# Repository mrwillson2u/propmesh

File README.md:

# PropMesh

Open-source wireless control for Halloween and holiday props.

Small ESP32 boards hidden in your props talk to each other by radio. A
sensor at the gate can set off a skeleton by the porch, a light show can
come on at dusk, and nothing needs wires across the lawn or an internet
connection. You set it all up from a web page, with no code.

**Using PropMesh?** Start at the docs site:
**[mrwillson2u.github.io/propmesh](https://mrwillson2u.github.io/propmesh/)**.
It has step-by-step guides, a page for each supported board, an installer
that puts the firmware on a board from your browser, and a copy of the
console you can try with no hardware.

This README is for people working on PropMesh itself.

> **Beta.** PropMesh runs the project's own yard for Halloween 2026 on
> off-the-shelf boards, and it changes quickly. Some features haven't
> been tried on real hardware yet. The docs site and
> [`docs/status.md`](docs/status.md) say which.

## What works today

The firmware runs on inexpensive ESP32 dev boards. You plug a board in,
open the console, and tell it what each pin does: relay, LED dimmer,
servo, DC motor, LED strip, or sensor. The board stores that and runs on
its own.

- **Mesh.** Boards pass messages to each other over ESP-NOW, so a far
  prop only needs to hear another board, not your WiFi. One board is the
  **bridge**: it connects the console to the mesh by USB or home WiFi and
  keeps the shared clock.
- **Shows.** Timed sequences across any outputs on any boards, triggers
  built as a graph (delay, cooldown, lockout, random pick, chains), a
  schedule tied to sunset, and STOP ALL. The show is stored on the boards
  and keeps running with the laptop closed.
- **Lights.** WS2812 and SK9822/APA102 strips, a fire effect, and BRMesh
  Bluetooth flood lights paired straight from the console.
- **Updates over the air,** through the mesh or over WiFi, resumable,
  with automatic rollback.
- **Battery boards.** Deep sleep, check-ins on a shared clock grid, and
  an optional repeater mode that relays while the show runs.
- **Yard view.** Mesh health by signal strength, and a map of your yard
  you can draw on.

| Board | Status |
|---|---|
| ESP32 DevKit V1 (30-pin) | Runs the project's yard |
| Adafruit HUZZAH32 Feather | Partly tested |
| ESP32-C6 SuperMini | Built, not yet flashed |
| ESP32-C3 SuperMini | Built, not yet flashed |

Each board's page on the docs site has the details. To support another
board, see [Adding a board](#adding-a-board).

## PropMesh's own boards (in design)

Two purpose-built boards run the same firmware and console. The PCBs
come after Halloween 2026, aiming at the 2027 season. Designs are in
[`hardware/`](hardware/) under CERN-OHL-S.

| | **PropMesh Pro** | **PropMesh Mini** |
|---|---|---|
| For | a prop that does everything | a small prop on a battery |
| MCU | ESP32-S3-WROOM-1 / 1U (N8R2) | ESP32-S3-WROOM-1U-N16R2 |
| Power | 12–30 V DC | 1S Li-ion |
| Motors | 2 stepper sockets (each can run 2 brushed DC) + 2 brushed DC | — |
| Servos | 6 | pending |
| Relays (dry contact, 30 V max) | 3 | pending |
| Addressable LED | 2 (3- or 4-wire) | pending |
| Dimmable LED | 6 | pending |
| Sensors | 3 digital, 2 analog | pending |
| Audio | I²S + microSD | I²S, sounds stored in flash |
| State | schematic done; layout next | module chosen; pin allocation being redone for the S3 |

"Pending" means the Mini's earlier ESP32-C3 plan was replaced on
2026-09-19 and its new allocation isn't finished. Neither board switches
mains power. That is a design decision; see [`CLAUDE.md`](CLAUDE.md).

## Origins

PropMesh grew out of one-off prop controllers built for the 2024 and
2025 seasons: a painlessMesh network of ESP32-C3s, a stepper-driven prop
lid, a fire-effect lantern, and a bridge for Bluetooth flood lights.
Those prototypes are kept in [`reference/`](reference/), with
credentials removed. This repository started in September 2026 to turn
them into one system.

## How it is tested

A feature counts as done when it has run on real boards. The host test
suite (`firmware/test/`) covers the pure logic: pin rules, show
scheduling, sunrise and sunset, ramps, mesh framing and reassembly.
Bench results, with dates and numbers, are recorded in
[`docs/generic-boards.md`](docs/generic-boards.md) next to each
feature's design; anything that has not yet run on hardware is marked
there, in [`docs/status.md`](docs/status.md), and on the docs site.

## Repository layout

```
docs/status.md          START HERE: where things stand, what's next, bench tests waiting
docs/generic-boards.md  the firmware that runs today: design, APIs, bench results per feature
docs/software-plan.md   architecture, mesh protocol, console plan, licensing
docs/hardware-spec.md   Pro and Mini: BOM, costs, mechanical, manufacturing

firmware/node/          the node firmware (PlatformIO), one env per board profile
firmware/common/        shared code: propmesh/ (mesh core, pure logic, generated
                        headers) and propmesh-node/ (drivers, API, sleep, OTA, sync)
firmware/test/          host tests (pio test -e native)
firmware/mesh-node/     the early ESP-NOW testbed (Sept 2026), kept building in CI

console/                the web console (Vite + React + TypeScript), with a simulator
website/                the docs site (Astro Starlight), browser flasher, screenshots

boards/                 SOURCE OF TRUTH: what each pin of a supported dev board can do
pinmap.yaml             SOURCE OF TRUTH: Pro / Mini pin assignments
schema/messages.yaml    SOURCE OF TRUTH: mesh messages and enums

tools/                  generators (genboards, genmsg, genpins), bridge.py, ota_serve.py,
                        and KiCad helpers for the hardware (checknet, checksetup, …)
hardware/               KiCad projects for the Pro and the Mini
reference/              pre-PropMesh prototypes (2024–25), scrubbed; see its README
```

Generated files are never edited by hand. Edit the source, regenerate,
and commit both. CI fails if they disagree.

```
python3 tools/genboards.py     # boards/*.yaml   -> boards_gen.h, boards_gen.ts
python3 tools/genmsg.py        # schema/*.yaml   -> proto_gen.h, proto_gen.ts
python3 tools/genpins.py       # pinmap.yaml     -> pins_*.h
# add --check to verify instead of write
```

## Getting started as a developer

You need Python 3, Node 22, and PlatformIO.

```
git clone https://github.com/mrwillson2u/propmesh.git && cd propmesh
git checkout dev
python3 -m venv .venv && . .venv/bin/activate
pip install -r requirements.txt platformio pyserial
npm ci --prefix console && npm ci --prefix website
```

**Firmware**

```
pio test -d firmware/test -e native                         # host tests
pio run  -d firmware/node -e esp32-devkit-v1                # build
pio run  -d firmware/node -e esp32-devkit-v1 -t upload      # flash a board on USB
```

Board envs: `esp32-devkit-v1`, `esp32-huzzah32`, `esp32-c6-supermini`,
`esp32-c3-supermini`. On Linux, USB serial needs your user in the
`dialout` group.

**Console**

```
npm run dev --prefix console        # then open http://localhost:5173/?sim=1
```

`?sim=1` connects to a simulated bridge with two boards behind it, so you
can work on the UI with no hardware. USB connections need Chrome or Edge.

**Docs site**

```
npm run dev --prefix website        # http://localhost:4321/propmesh/
```

`website/README.md` covers the board pages, the flasher, the screenshots
and how to write a page.

**Talking to a live mesh from a terminal**

```
python3 tools/bridge.py --host propmesh.local status
```

This reaches the bridge over WiFi, so nothing gets reset by opening a USB
port. `docs/status.md` §5 covers working on a separate server, tunnels,
and serving firmware for updates.

## Adding a board

A board works with PropMesh once it has a **profile**: a YAML file in
[`boards/`](boards/) listing what each pin can do and what to warn about.

1. Copy an existing profile and fill it in from the seller's pinout and
   the chip datasheet's strapping-pin table.
2. Add its `board_type` to `BoardType` in `schema/messages.yaml`.
3. Run `python3 tools/genmsg.py && python3 tools/genboards.py`. The
   generator refuses advice the pin can't follow.
4. Add an env to `firmware/node/platformio.ini` with
   `-DPM_BOARD_PROFILE=PM_BOARD_<ID>`.

The board's page on the docs site and its pinout in the console are
generated from the same file. Not comfortable doing this? Use the
[board request form](https://github.com/mrwillson2u/propmesh/issues/new?template=board-request.yml).

## Contributing

Pull requests go to **`dev`**. `main` only takes PRs from `dev` and
publishes the docs site. Read [`CONTRIBUTING.md`](CONTRIBUTING.md) first:
it has the checks to run and the sign-off each commit needs.

The decisions in [`CLAUDE.md`](CLAUDE.md) under "Locked design decisions"
were settled after analysis. To change one, say why its reasoning no
longer holds. Bugs, questions and reports from real yards go in
[issues](https://github.com/mrwillson2u/propmesh/issues).

## License

Copyleft open source: use it, change it, sell things built with it, but
share your changes and keep the credit. Details and reasoning:
[`LICENSING.md`](LICENSING.md).

| Part | License |
|---|---|
| Firmware, tools, board profiles | GPL-3.0-or-later |
| Console (web app) | AGPL-3.0-or-later |
| Board designs (`hardware/`) | CERN-OHL-S-2.0 |
| Docs and the docs site's text | CC BY-SA 4.0 |

The PropMesh name and logo: [`TRADEMARK.md`](TRADEMARK.md). Credits and
third-party code: [`THIRD_PARTY.md`](THIRD_PARTY.md).

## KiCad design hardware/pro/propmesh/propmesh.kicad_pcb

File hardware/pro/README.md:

# PropMesh Pro — start here

KiCad project: `propmesh/`. This file is the **map** — if you ever need
two documents open at once to do one task, that's a bug in the docs;
fix the doc, don't cross-reference.

## The four layers

| Layer | Lives in | Open it when |
|---|---|---|
| **WHY** — decisions, costs, schedule | `docs/hardware-spec.md` | you're questioning a choice or pricing something. Its BOM tables are **cost rollups, not orderable specs.** |
| **WHAT** — every pin and net name | `pinmap.yaml` (repo root) | never during capture — each sheet file below already quotes its nets. Edit it only to *change* an assignment (then regenerate + update spec, same commit). |
| **HOW (layout)** — placing and routing the board | **`layout.md`** | laying out the PCB as one numbered procedure (Part A: Board Setup, outline, holes, every connector's Position X/Y, block regions, per-part placement tables, zones, routing, silk, DRC, export) with a "where you are" line at the top; Part B is the reference behind it. `tools/checksetup.py` verifies the setup steps from the saved files. |
| **HOW** — drawing each schematic sheet | **`sheets/NN-*.md`** | drawing that sheet. Each is self-contained: parts, selection criteria, supporting passives, exact net names, a done-checklist. |
| **PROCESS** — review, libraries, git | `CLAUDE.md` (review order), `hardware/README.md` (libraries, easyeda2kicad, what's committed) | reviewing, importing a part, committing. |
| **AUDIT** — the last full review | **`review-2026-09-08.md`** | before routing, and before ordering. One pre-route audit of schematic + placement + every datasheet: what must be fixed first, what was verified correct, and what to check at bring-up. |

**The standing rule:** anything learned during capture — a criteria
gotcha, a stock problem, a changed value — goes into the relevant
`sheets/` file the same day. Chat sessions and heads are not storage.

**Connections live in `NN-name.net.yaml`, one line per net — never in
prose or markdown tables — and are DRAWN, not described.**
`tools/checknet.py NN.net.yaml --mermaid` renders it to
`NN.diagram.html` (open in any browser) and `NN.diagram.md`: one
left-to-right wiring diagram per circuit block, every part's GND pin
written in its box, plus a per-net roll-call table. That is the drawing
guide Colin works from — visual, not prose. **A multi-unit symbol (quad
gate, dual op-amp) must carry `units: {A: [pins], …}` in its yaml** so
the diagram draws one box per unit, matching the separate symbols KiCad
places — sheet 05's 74AHCT125 rendered as one 14-pin box first, and
was undrawable from (2026-09-05). The markdown says *why*; the
yaml says *what wires to what*, and it is machine-checked:

```
python3 tools/checknet.py hardware/pro/sheets/01-power.net.yaml
```

diffs the spec against `kicad-cli`'s netlist export of the real
schematic **and writes `NN.check.html` — the same diagram coloured by
result** (green ok, red wrong net with a note saying where the pin
actually is, orange wrong value, dashed not placed). Open it in a
browser, not the editor; all green = sheet done. Parts match by
**Value**, and each spec part is paired with one specific KiCad part
(same-value parts are paired by best fit, so a finding names the
actual resistor; boxes show `C_bulk = C11`). A part still carrying its
symbol's default Value is matched by symbol and flagged. Nets match by
membership (internal nodes need no labels), and the named rails are
checked for their label. This closes the "schematic disagrees with the design" bug
class CLAUDE.md ranks first. The markdown keeps only a **designator
cross-reference** where the sheet's names differ from the datasheet
figure's. Sheet 01 is the worked example; **all seven `.net.yaml`s are
written** (05/07 landed 2026-09-04).

**Every part gets a TABLE ROW, never only prose.** A part described in
a sentence ("plus a 10 kΩ pull-up", "gate network: a zener and 100 kΩ")
is invisible when you work down the table sourcing parts — it was a real
miss on sheet 01's gate clamp. Each sheet ends with a **Complete parts
list**: one row per reference designator, and if it is not in that table
it does not exist.

**One list, not three.** Parts are itemised in **the sheet's
per-section tables and nowhere else** — that is the single source. The
spec's §2.4 carries only a **rolled-up cost** per block and points at
the sheet; a sheet's "Sourcing status" tracks only what is still
*missing*, never a second copy of what is found. This was learned the
hard way: the same 28 parts briefly existed in three places, guaranteed
to drift. **When a sheet is finished, update its §2.4 rollup total and
re-run the cost cascade** — one number to sync, not thirty rows.

## Sheet status

| Sheet | Doc | Drawn | Open ⚠ items in doc |
|---|---|---|---|
| 01 Power | `sheets/01-power.md` — **done: every part has a verified LCSC number, tier and price** | **☑ DONE 2026-09-03** — checknet all green incl. J2, ERC clean, all 5 imported land patterns datasheet-verified, C4 DNP set; **staged-power link headers J48/J49/J50 added 2026-09-07** (spec §2.6), checker green, ERC clean | for LAYOUT: J1 pad ring ≥2.8 mm; silkscreen `ONE SUPPLY ONLY` / `+ TIP`; measure a real F1 holder at bring-up |
| 02 MCU + USB | `sheets/02-mcu-usb.md` — **fully sourced** | **☑ DONE 2026-09-04** — checknet all nets + footprints green; ERC clean bar the 32 expected one-sided labels | for LAYOUT: USB-C needs its shield vias; TP37 silkscreen |
| 03 Slow outputs | `sheets/03-outputs.md` — **fully sourced**, 6 supply-voltage switch/dim channels + flybacks | **☑ DONE 2026-09-04** — checknet all green, ERC clean | for BRING-UP: relay NO/NC continuity beep; `C723982` stock thin (82); silk: NO\|COM\|NC, 30V warning, V+/SW, `V+ = SUPPLY VOLTAGE` |
| 04 Audio + SD | `sheets/04-audio.md` — **fully sourced**, GAIN/SD_MODE datasheet-exact, line-out via PCM5102A | **☑ DONE 2026-09-04** — checknet all green, ERC clean | for BRING-UP: meter the jack tip/ring/sleeve (three numbering schemes collided — see doc); `C723982` shared stock pool |
| 05 Addressable LED | `sheets/05-led.md` — **fully sourced**; both strips 3/4-wire through **one octal SN74AHCT541DWR `C2682058`** (3 spare 5 V outputs), 2× DG128-02P per strip, no mode jumpers, status pixel import verified | **☑ DONE 2026-09-06** — checknet all green, ERC clean (whole project: 0 violations) | for LAYOUT: silk 5 V-injection note at strip terminals; 02P pairs butt together as one 4-pole; only remaining Economic-PCBA risk part is the status pixel (check in JLC order UI before a PCBA run) |
| 06 Motors | `sheets/06-motors.md` — **fully sourced**, row spacing 12.70 mm (Pololu-verified), ILIM = 2.13 A, RST/SLP-tie = UART bus | **☑ DONE 2026-09-04** — checknet all green, ERC clean | for LAYOUT: socket rows exactly 12.70 mm, DRV8871 EP paste vs TI drawing, silk TMC strap defaults |
| 07 Sensors + expansion | `sheets/07-sensors-expansion.md` — **fully sourced**: Qwiic = SH-1.0 clone `C7430446` (genuine JST dead). **IR receiver dropped 2026-09-05** (hidden board → plug-in on a DIGITAL_IN) | **☑ DONE 2026-09-06** — IR block deleted, checknet all green, ERC clean | ⚠ layout: measure Qwiic clone vs JST-SH footprint; silk KEEP LOW AT RESET at exp pins 4/5, 5V\|GND\|SIG at all six sensor headers |
| 08 Test points | `sheets/08-testpoints.md` — 33 GPIO pads + 6 rail pads + DNP strap pad, spec §2.6 | **☑ DONE 2026-09-07** — labels generated from the yaml, checknet green, ERC clean | pads go beside each net's owner, silk = net name |

> **Superseded on 2026-09-08 by `review-2026-09-08.md`:** ERC is **not** 0 —
> `C1` (the EN reset cap) came unwired in the uncommitted MCU-sheet edit, and
> sheet 06 carries the label `MA_ILIM` twice so both DRV8871 ILIM pins share one
> net. Both are blockers; the review lists them with everything else found.

**All eight sheets captured; ERC 0; board synced 239/239 footprints; Board Setup, outline, origin, holes done and every part placed by `tools/placeboard.py` (2026-09-07, DRC clean for placement — `layout-placement.png`).** Schematic work is done unless layout turns something up. Layout per `layout.md` Part A — the ⚠ column above and its step A19 are the layout to-do list.

## Rules that apply to every sheet

- **The schematic uses STANDARD sequential designators; the yaml uses
  descriptive spec names.** Settled 2026-09-06, when the whole board was
  renumbered to `R1…R52`, `C1…C47`, `J1…J47` (prefix taken from each
  symbol's own library default, numbered per sheet in KiCad's sheet
  order). Standard refs are what assembly houses, BOM/CPL exports and
  every other contributor expect, and KiCad's annotation tools work
  *with* them — hand-written refs cost three separate debugging
  sessions (a `C_A1` collision across two sheets, refs ending in letters
  blocking annotation, a triple-duplicated connector). Nothing is lost:
  the yaml keeps `R_ILA`/`C_B1`-style names because they say what a part
  is, and **`checknet.py` pairs the two by Value and prints both**
  (`R22 (R_ILA)`). Spec names must still be unique across sheets, since
  a duplicate there confuses the pairing.
  *To find a part during layout, cross-probe* — click it in the
  schematic and it highlights in the PCB editor; footprints also import
  grouped by sheet. That is the job descriptive refs were doing.
- **Net names = pinmap signal names, exactly.** That's what lets the
  netlist be checked against `pinmap.yaml` mechanically.
- **Power rails cross sheets by NAME — one canonical name each.** KiCad
  power symbols are global, so `+5V` on one sheet is `+5V` on all of
  them. The board's rails are exactly: **`GND`, `+5V`, `+3V3`,
  `VIN_RAW`, `VIN_PROT`** (all created on sheet 01). A second name for
  the same rail silently produces a second, unpowered net — sheet 06
  briefly called `VIN_PROT` "VMOT" (the stepper-datasheet name) and
  would have left the motor drivers dead. **If a datasheet names a pin
  differently, that goes in a note, never on the label.**
- **Passives: one package — 0603.** Resistors: **1 % thick film,
  1/10 W default** (Basic 1 % 0603 coverage is deep; 5 % saves
  nothing). Caps: **X7R only — never Y5V/Z5U**, whose capacitance
  collapses with temperature and bias; this board lives outdoors in
  late October. **Check DC-bias derating on every MLCC ≥1 µF** (a
  10 µF/16 V part at 12 V is ~3 µF).
- **Screw terminals: one family for the whole board — DEGSON, decided
  2026-09-03.** Every field-wiring terminal on every sheet comes from
  this list; do not browse the category again.

  | Use | Pitch | Part | LCSC |
  |---|---|---|---|
  | DC in (J1), DC motor ×2, **LED strip halves ×4** | 5.0 | DG128-5.0-**02P**-14-00A(H) | `C711349` |
  | Relay ×3 | 5.0 | DG128-5.0-**03P**-14-00A(H) | `C691861` |
  | LED strips ×2 | 5.0 | ~~DG128-5.0-04P~~ **stock-dead 2026-09-04 → 2× 02P per strip** (5V/GND + DATA/CLK); both strips 3/4-wire since 2026-09-05 | `C711349` ×4 |
  | Speaker, LED outputs | 3.5 | DG381S-3.5-**02P**-14-00A(H) | `C723982` |

  All are **fixed, side-entry, THT, 300 V** — 5.0 mm pitch is
  interchangeable with 5.08 at these pin counts. The 3.5 mm family is
  for low-current outputs that take thin wire; consolidating them onto
  5.08 would drop a part family (§4.3) at ~9 mm of board edge — a v0.2
  call.

  **Barrier blocks (Mean Well style) considered 2026-09-03 and
  rejected.** Every 7.62 mm barrier block in the category (KF7.62,
  DBT10/30/50) takes the same **12–22 AWG / 2.5 mm²** as the DG128 —
  the bigger M3 screw does not mean bigger wire. And it terminates
  *worse* for this audience: flat screw heads want crimped fork lugs
  (that is how a Mean Well's own manual wires them), while bare
  stranded wire splays and creeps loose under them; the DG128's rising
  cage clamps bare wire properly, which is what users actually bring.
  Barrier screws also face up, fighting the side-entry gland enclosure.
  The system's lug-friendly barrier block already exists — on the
  Mean Well itself.

  **Pluggable (2EDG) was considered and deferred.** DEGSON's
  2EDGR header (`C699495`, 02P, ~$0.05) + 2EDGK plug is roughly
  cost-neutral and lets a user unplug a whole prop — genuinely better
  for seasonal re-wiring. It was *not* chosen for v0.1 because the
  plugs are friction-fit and the locked decision picked screw terminals
  precisely for cables that get yanked in a yard; a snagged cable can
  unplug a 2EDG. Revisit after a season with the box, with the flanged
  2EDGKM variants in mind if yank-resistance is the only objection.
- **Connector orientation is a decision, not a default.** The enclosure
  (spec §2.3, decided 2026-09-06: Multilink RNI-1500, the CG-1500
  successor the pixel community standardised on) takes wires through
  self-sealing ports along its **bottom** edge, so field-wiring
  connectors sit on the bottom edge and the two short edges (the full
  run is ~250 mm; one edge was never possible) and service items (USB,
  SD, antenna, button) on the top edge — pick vertical vs
  right-angle entry per connector *before* layout, because the
  footprints differ and rework means desoldering.
- **You are committing to FOOTPRINTS, not part numbers.** Production is
  a year out; no stock level survives that, and a sourcing pass before
  v0.2 is happening regardless. So judge a part by *what a future
  substitution costs*:
  - **Free swap** (standard land pattern, many vendors): all 0603/0805
    R and C, SOD-123/SMA diodes, SOT-23 / TO-252 semis, EIA-size MLCCs.
    Thin stock here is not worth worrying about — take what is
    available and move on.
  - **Costs a layout change**: **inductors** (molded footprints vary by
    family — the single most under-appreciated respin risk), fuse
    holders, connectors, and anything with a vendor-specific land
    pattern. **Spend the verification effort here**, and prefer a part
    whose footprint matches a family with several members.
- **Part picking order: JLC Basic → in stock in quantity → package.**
  Price is a tiebreaker, not a criterion — an Extended part costs $3/run
  in feeder fees before its unit price matters.
- **Brand tier: generic for commodity, premium only where it earns it.**
  Samsung / Yageo / Fenghua / Uniroyal MLCCs and resistors are 2–3×
  cheaper than Murata / TDK and entirely adequate for decoupling and
  bulk. Pay up only where a spec actually depends on it (tight-tolerance
  feedback dividers, a timing part, low-ESR at high ripple). A Murata
  10 µF is $0.27; the generic equivalent is ~$0.10 and does the same job
  here.
- **Voltage rating is a hard limit, not a derating knob.** Check the
  part's rating against the **maximum** rail it sees (30 V input here,
  not 12 V nominal) before looking at anything else — then apply DC-bias
  derating on top, which is a separate, additional loss of capacitance.
- **LCSC filters: filter on primaries, SORT on secondaries.** Primary
  attributes (value, voltage, package, dielectric, type) are populated
  reliably. Secondary ones (Isat, DCR, ESR, ripple current) are often
  blank or wrong — and **filtering on a blank field silently drops the
  part**, which is why stacking every requirement as a filter returns
  junk or nothing. Filter the primaries, sort by the secondary, read the
  column, then **verify the final 2–3 candidates on the manufacturer
  datasheet**. The distributor table builds a shortlist; it is not the
  source of truth for a spec the design depends on.
- **Check the value actually exists in the family before specifying
  it.** Power inductors ladder on **E6** (1.0/1.5/2.2/3.3/4.7/6.8/10),
  not E12 — a datasheet's "5.5 µH" has no stocked neighbour at 5.6 µH.
  Same trap for electrolytic values and 1 % resistors: pick from what
  the category filter actually returns, then re-run the math on that
  value rather than the ideal one.
- **LCSC navigation, as it actually is** (verified 2026-09-02): there
  is no "Power Inductors" category — inductors are all under
  **Passives → Inductors, Coils, Chokes → Fixed Inductors**, narrowed
  by sortable columns. Two of those columns are **"Current Rating"**
  (thermal/RMS) and **"Current - Saturation (Isat)"** — *different
  numbers*; margin is computed against Isat. Filtering the wrong
  column is how an 0805 110 mA part survives a search for a 3 A buck.
  Generally: **the spec that matters is often a distinct column from
  the one named in the part title.**
- **The MPN suffix IS the package** (AP64350**SP** = SO-8EP,
  PCA9685**PW** = TSSOP-28). For ICs there is no footprint "choice" —
  ordering the part decides it. Choices exist only for generics.
- **Hot air is available** at this bench — TQFN/SOT-563 are buildable.
  Prefer bigger packages anyway when free: v0.1 wants probe access and
  reworkability more than area.
- After every schematic session: **F8** (Update PCB from Schematic),
  save, commit.

**`checknet.py` assertions** (each was added after a bug got past it):
symbol pin numbers ⊆ footprint pad numbers (sheet 01's FET, 2026-09-06);
per-unit diagram boxes for multi-unit symbols (2026-09-05); and
**distinct spec nets must resolve to distinct schematic nets** — two
spec nets collapsing into one means the schematic shorts them, and each
still scores clean on its own (`MA_ILIM`/`MB_ILIM`, found by an external
audit 2026-09-08, not by the checker).

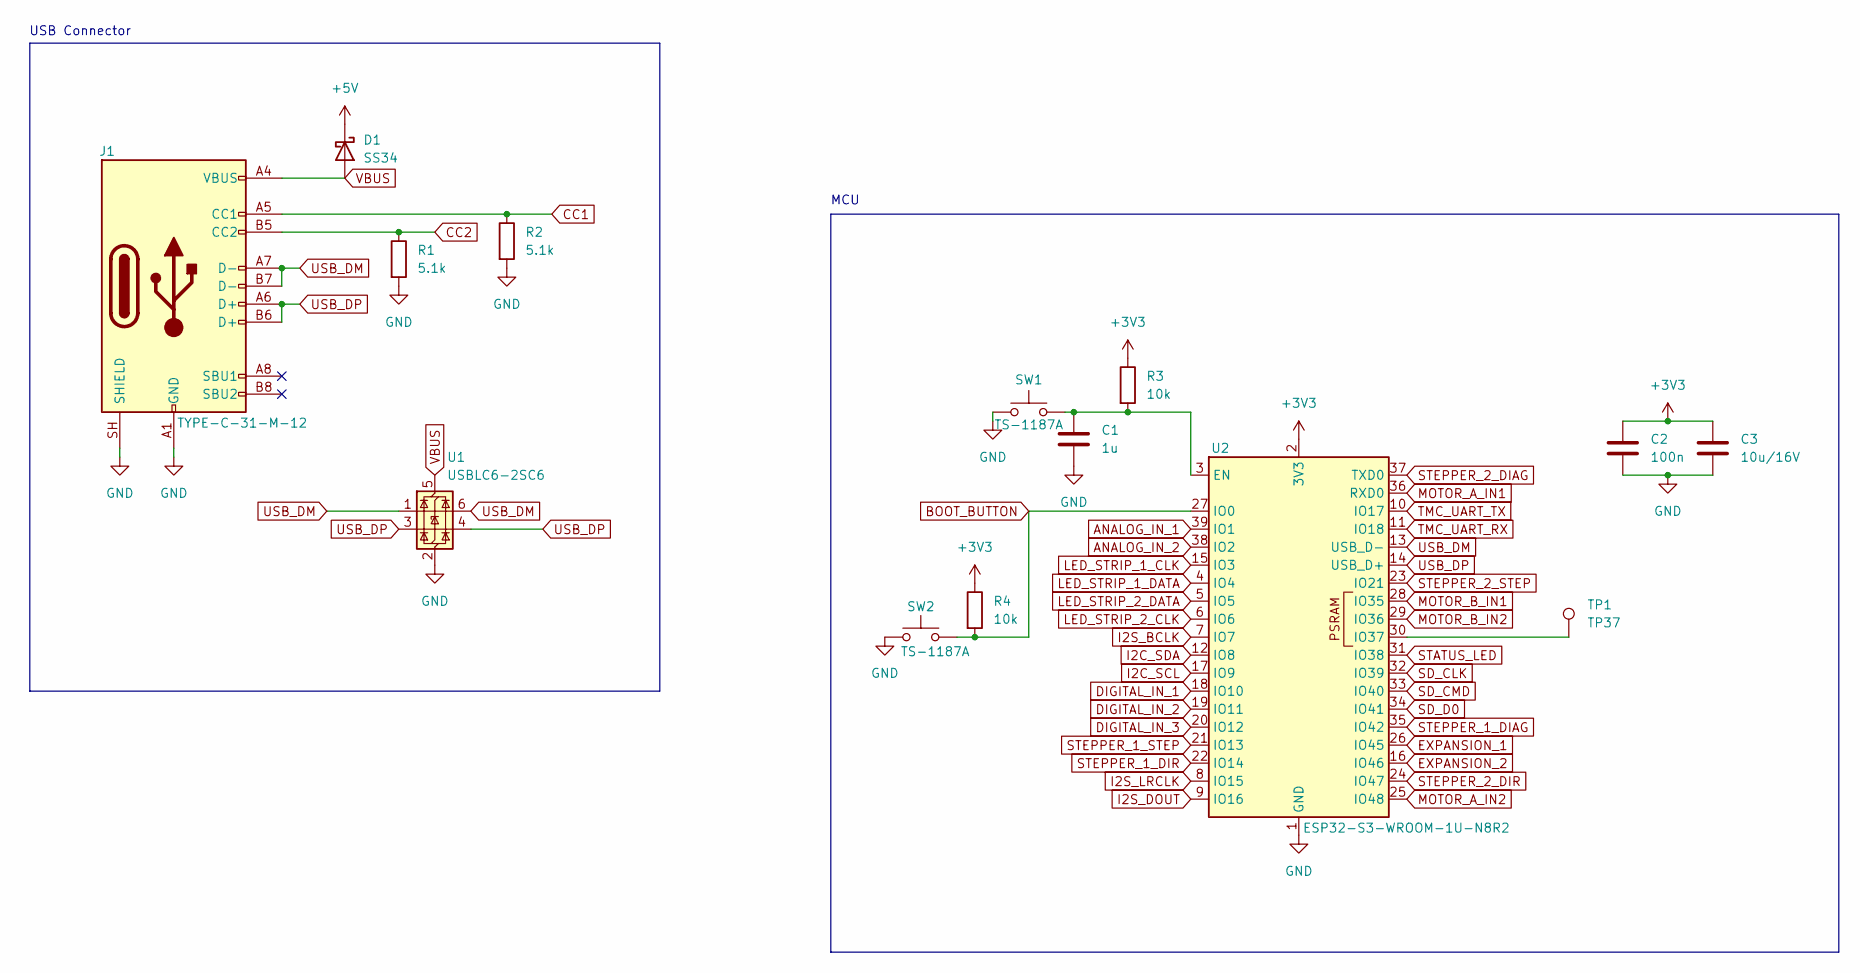
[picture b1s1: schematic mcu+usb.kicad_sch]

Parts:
C1: 1u; C_0603_1608Metric
C2: 100n; C_0603_1608Metric
C3: 10u/16V; C_0805_2012Metric
D1: SS34; D_SMA
J1: TYPE-C-31-M-12; USB_C_Receptacle_HRO_TYPE-C-31-M-12
R1, R2: 5.1k; R_0603_1608Metric
R3, R4: 10k; R_0603_1608Metric
SW1, SW2: TS-1187A; SW_Push_1P1T_XKB_TS-1187A
TP1: TP37; TestPoint_Pad_1.5x1.5mm
U1: USBLC6-2SC6; SOT-23-6
U2: ESP32-S3-WROOM-1U-N8R2; ESP32-S3-WROOM-1U

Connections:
+3V3: C2.1, C3.1, R3.1, R4.1, U2.2 (3V3); also elsewhere on the board
ANALOG_IN_1: U2.39 (IO1); also elsewhere on the board
ANALOG_IN_2: U2.38 (IO2); also elsewhere on the board
BOOT_BUTTON: R4.2, SW2.2, U2.27 (IO0); also elsewhere on the board
CC1: J1.A5 (CC1), R2.1
CC2: J1.B5 (CC2), R1.1
DIGITAL_IN_1: U2.18 (IO10); also elsewhere on the board
DIGITAL_IN_2: U2.19 (IO11); also elsewhere on the board
DIGITAL_IN_3: U2.20 (IO12); also elsewhere on the board
EXPANSION_1: U2.26 (IO45); also elsewhere on the board
EXPANSION_2: U2.16 (IO46); also elsewhere on the board
GND: C1.2, C2.2, C3.2, J1.A1 (GND), J1.A12 (GND), J1.B1 (GND), J1.B12 (GND), J1.SH (SHIELD), R1.2, R2.2, SW1.1, SW2.1, U1.2 (GND), U2.1 (GND), U2.40 (GND), U2.41 (GND); also elsewhere on the board
I2C_SCL: U2.17 (IO9); also elsewhere on the board
I2C_SDA: U2.12 (IO8); also elsewhere on the board
I2S_BCLK: U2.7 (IO7); also elsewhere on the board
I2S_DOUT: U2.9 (IO16); also elsewhere on the board
I2S_LRCLK: U2.8 (IO15); also elsewhere on the board
LED_STRIP_1_CLK: U2.15 (IO3); also elsewhere on the board
LED_STRIP_1_DATA: U2.4 (IO4); also elsewhere on the board
LED_STRIP_2_CLK: U2.6 (IO6); also elsewhere on the board
LED_STRIP_2_DATA: U2.5 (IO5); also elsewhere on the board
MOTOR_A_IN1: U2.36 (RXD0); also elsewhere on the board
MOTOR_A_IN2: U2.25 (IO48); also elsewhere on the board
MOTOR_B_IN1: U2.28 (IO35); also elsewhere on the board
MOTOR_B_IN2: U2.29 (IO36); also elsewhere on the board
unnamed 116: D1.1 (K); also elsewhere on the board
unnamed: C1.1, R3.2, SW1.2, U2.3 (EN)
SD_CLK: U2.32 (IO39); also elsewhere on the board
SD_CMD: U2.33 (IO40); also elsewhere on the board
SD_D0: U2.34 (IO41); also elsewhere on the board
STATUS_LED: U2.31 (IO38); also elsewhere on the board
STEPPER_1_DIAG: U2.35 (IO42); also elsewhere on the board
STEPPER_1_DIR: U2.22 (IO14); also elsewhere on the board
STEPPER_1_STEP: U2.21 (IO13); also elsewhere on the board
STEPPER_2_DIAG: U2.37 (TXD0); also elsewhere on the board
STEPPER_2_DIR: U2.24 (IO47); also elsewhere on the board
STEPPER_2_STEP: U2.23 (IO21); also elsewhere on the board
TMC_UART_RX: U2.11 (IO18); also elsewhere on the board
TMC_UART_TX: U2.10 (IO17); also elsewhere on the board
VBUS: D1.2 (A), J1.A4 (VBUS), J1.A9 (VBUS), J1.B4 (VBUS), J1.B9 (VBUS), U1.5 (VBUS); also elsewhere on the board

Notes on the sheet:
MCU
USB Connector

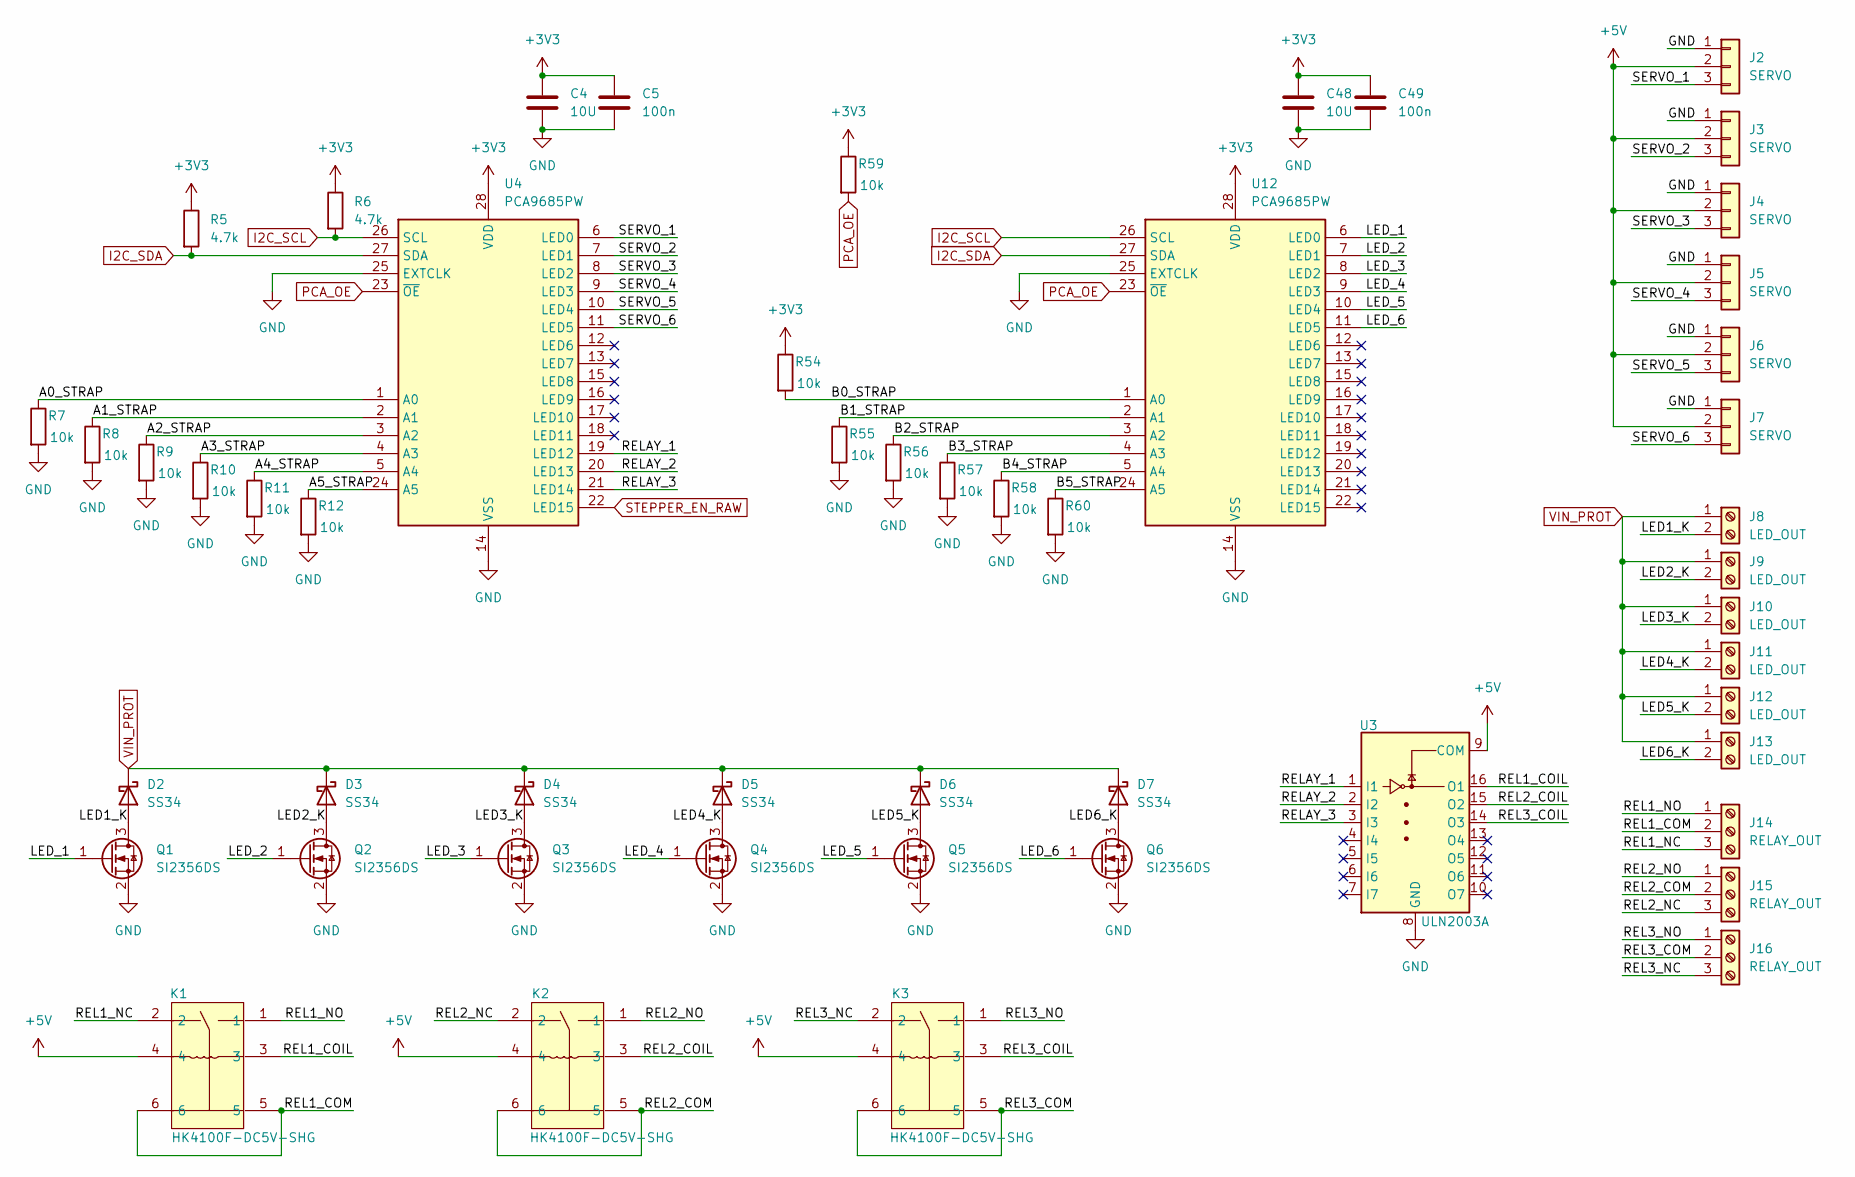
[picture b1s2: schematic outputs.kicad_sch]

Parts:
C4, C48: 10U; C_0805_2012Metric
C5, C49: 100n; C_0603_1608Metric
D2, D3, D4, D5, D6, D7: SS34; D_SMA
J2, J3, J4, J5, J6, J7: SERVO; PinHeader_1x03_P2.54mm_Vertical
J8, J9, J10, J11, J12, J13: LED_OUT; CONN-TH_DG381S-3.5-02P-14-00A-H
J14, J15, J16: RELAY_OUT; CONN-TH_DG128-5.0-03P-14-00A-H
K1, K2, K3: HK4100F-DC5V-SHG; RELAY-TH_HK4100F-DC5V-SHG; MPN HK4100F-DC5V-SHG; LCSC Part C12072
Q1, Q2, Q3, Q4, Q5, Q6: SI2356DS; SOT-23
R5, R6: 4.7k; R_0603_1608Metric
R7, R8, R9, R10, R11, R12, R54, R55, R56, R57, R58, R59, R60: 10k; R_0603_1608Metric
U3: ULN2003A; SOIC-16_3.9x9.9mm_P1.27mm
U4, U12: PCA9685PW; TSSOP-28_4.4x9.7mm_P0.65mm

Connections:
+3V3: C4.1, C5.1, C48.1, C49.1, R5.1, R6.1, R54.1, R59.1, U4.28 (VDD), U12.28 (VDD); also elsewhere on the board
+5V: J2.2, J3.2, J4.2, J5.2, J6.2, J7.2, K1.4, K2.4, K3.4, U3.9 (COM); also elsewhere on the board
/Outputs/A0_STRAP: R7.1, U4.1 (A0)
/Outputs/A1_STRAP: R8.1, U4.2 (A1)
/Outputs/A2_STRAP: R9.1, U4.3 (A2)
/Outputs/A3_STRAP: R10.1, U4.4 (A3)
/Outputs/A4_STRAP: R11.1, U4.5 (A4)
/Outputs/A5_STRAP: R12.1, U4.24 (A5)
/Outputs/B0_STRAP: R54.2, U12.1 (A0)
/Outputs/B1_STRAP: R55.1, U12.2 (A1)
/Outputs/B2_STRAP: R56.1, U12.3 (A2)
/Outputs/B3_STRAP: R57.1, U12.4 (A3)
/Outputs/B4_STRAP: R58.1, U12.5 (A4)
/Outputs/B5_STRAP: R60.1, U12.24 (A5)
/Outputs/LED1_K: D2.2 (A), J8.2, Q1.3 (D)
/Outputs/LED2_K: D3.2 (A), J9.2, Q2.3 (D)
/Outputs/LED3_K: D4.2 (A), J10.2, Q3.3 (D)
/Outputs/LED4_K: D5.2 (A), J11.2, Q4.3 (D)
/Outputs/LED5_K: D6.2 (A), J12.2, Q5.3 (D)
/Outputs/LED6_K: D7.2 (A), J13.2, Q6.3 (D)
/Outputs/LED_1: Q1.1 (G), U12.6 (LED0)
/Outputs/LED_2: Q2.1 (G), U12.7 (LED1)
/Outputs/LED_3: Q3.1 (G), U12.8 (LED2)
/Outputs/LED_4: Q4.1 (G), U12.9 (LED3)
/Outputs/LED_5: Q5.1 (G), U12.10 (LED4)
/Outputs/LED_6: Q6.1 (G), U12.11 (LED5)
/Outputs/REL1_COIL: K1.3, U3.16 (O1)
/Outputs/REL1_COM: J14.2, K1.5, K1.6
/Outputs/REL1_NC: J14.3, K1.2
/Outputs/REL1_NO: J14.1, K1.1
/Outputs/REL2_COIL: K2.3, U3.15 (O2)
/Outputs/REL2_COM: J15.2, K2.5, K2.6
/Outputs/REL2_NC: J15.3, K2.2
/Outputs/REL2_NO: J15.1, K2.1
/Outputs/REL3_COIL: K3.3, U3.14 (O3)
/Outputs/REL3_COM: J16.2, K3.5, K3.6
/Outputs/REL3_NC: J16.3, K3.2
/Outputs/REL3_NO: J16.1, K3.1
/Outputs/RELAY_1: U3.1 (I1), U4.19 (LED12)
/Outputs/RELAY_2: U3.2 (I2), U4.20 (LED13)
/Outputs/RELAY_3: U3.3 (I3), U4.21 (LED14)
/Outputs/SERVO_1: J2.3, U4.6 (LED0)
/Outputs/SERVO_2: J3.3, U4.7 (LED1)
/Outputs/SERVO_3: J4.3, U4.8 (LED2)
/Outputs/SERVO_4: J5.3, U4.9 (LED3)
/Outputs/SERVO_5: J6.3, U4.10 (LED4)
/Outputs/SERVO_6: J7.3, U4.11 (LED5)
GND: C4.2, C5.2, C48.2, C49.2, J2.1, J3.1, J4.1, J5.1, J6.1, J7.1, Q1.2 (S), Q2.2 (S), Q3.2 (S), Q4.2 (S), Q5.2 (S), Q6.2 (S), R7.2, R8.2, R9.2, R10.2, R11.2, R12.2, R55.2, R56.2, R57.2, R58.2, R60.2, U3.8 (GND), U4.14 (VSS), U4.25 (EXTCLK), U12.14 (VSS), U12.25 (EXTCLK); also elsewhere on the board
I2C_SCL: R6.2, U4.26 (SCL), U12.26 (SCL); also elsewhere on the board
I2C_SDA: R5.2, U4.27 (SDA), U12.27 (SDA); also elsewhere on the board
STEPPER_EN_RAW: U4.22 (LED15); also elsewhere on the board
VIN_PROT: D2.1 (K), D3.1 (K), D4.1 (K), D5.1 (K), D6.1 (K), D7.1 (K), J8.1, J9.1, J10.1, J11.1, J12.1, J13.1; also elsewhere on the board

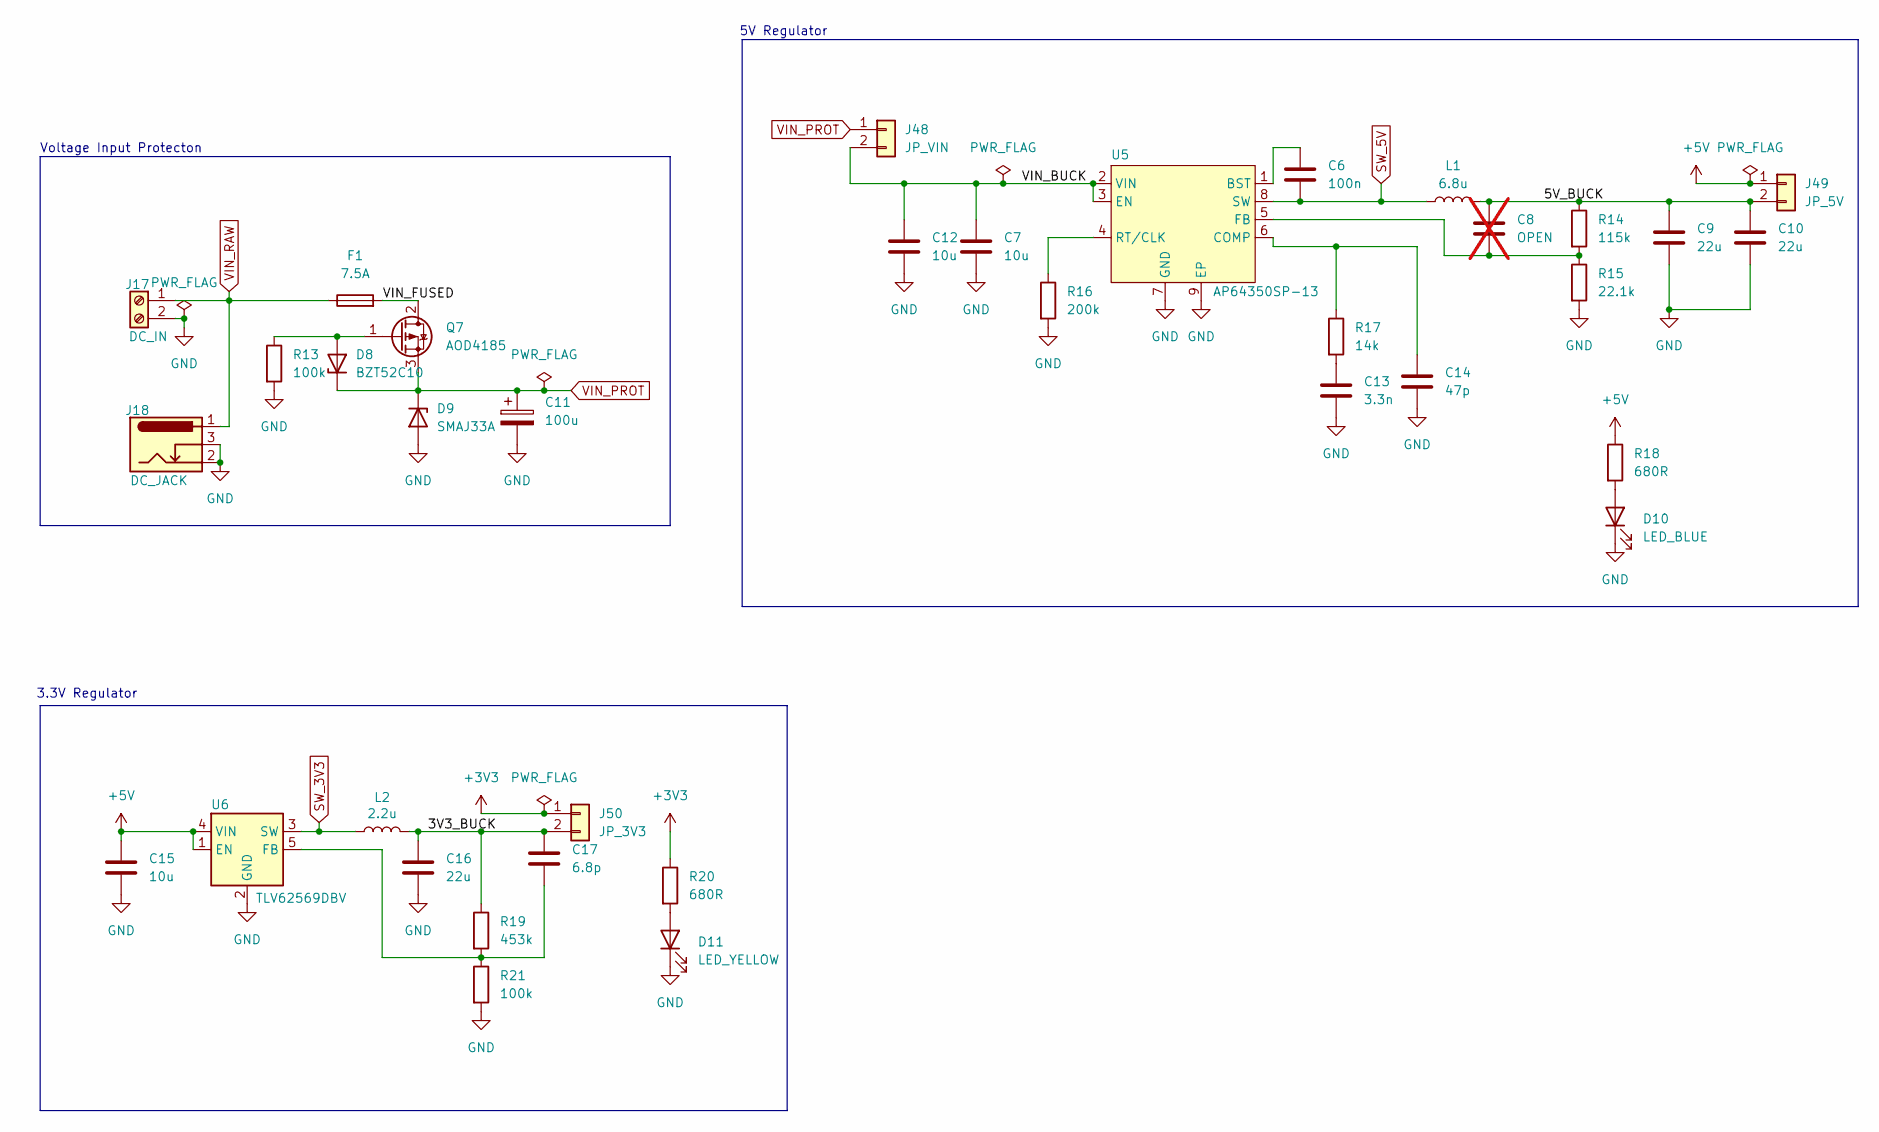
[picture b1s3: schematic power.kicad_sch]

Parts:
C6: 100n; C_0603_1608Metric
C7, C12: 10u; C_1210_3225Metric
C8: OPEN; C_0603_1608Metric; not fitted
C9, C10, C16: 22u; C_1206_3216Metric
C11: 100u; CP_Elec_8x10.5
C13: 3.3n; C_0603_1608Metric
C14: 47p; C_0603_1608Metric
C15: 10u; C_0805_2012Metric
C17: 6.8p; C_0603_1608Metric
D8: BZT52C10; D_SOD-123
D9: SMAJ33A; D_SMA
D10: LED_BLUE; LED_0603_1608Metric
D11: LED_YELLOW; LED_0603_1608Metric
F1: 7.5A; 01530008Z
J17: DC_IN; CONN-TH_DG128-5.0-02P-14-00A-H
J18: DC_JACK; DC-IN-TH_DC-044A-20A
J48: JP_VIN; PinHeader_1x02_P2.54mm_Vertical
J49: JP_5V; PinHeader_1x02_P2.54mm_Vertical
J50: JP_3V3; PinHeader_1x02_P2.54mm_Vertical
L1: 6.8u; IND-SMD_L11.5-W10.0
L2: 2.2u; IND-SMD_L7.1-W6.6
Q7: AOD4185; TO-252-2
R13, R21: 100k; R_0603_1608Metric
R14: 115k; R_0603_1608Metric
R15: 22.1k; R_0603_1608Metric
R16: 200k; R_0603_1608Metric
R17: 14k; R_0603_1608Metric
R18, R20: 680R; R_0603_1608Metric
R19: 453k; R_0603_1608Metric
U5: AP64350SP-13; SO-8_L4.9-W3.9-P1.27-LS6.0-BL-EP; MPN AP64350SP-13; LCSC Part C2071691
U6: TLV62569DBV; SOT-23-5

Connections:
+3V3: J50.1, R20.1; also elsewhere on the board
+5V: C15.1, J49.1, R18.1, U6.1 (EN), U6.4 (VIN); also elsewhere on the board
/Power/3V3_BUCK: C16.1, C17.1, J50.2, L2.2, R19.1
/Power/5V_BUCK: C8.1, C9.1, C10.1, J49.2, L1.2, R14.1
/Power/VIN_BUCK: C7.1, C12.1, J48.2, U5.2 (VIN), U5.3 (EN)
/Power/VIN_FUSED: F1.2, Q7.2 (D)
GND: C7.2, C9.2, C10.2, C11.2, C12.2, C13.2, C14.2, C15.2, C16.2, D9.2 (A), D10.1 (K), D11.1 (K), J17.2, J18.2, J18.3, R13.2, R15.2, R16.2, R21.2, U5.7 (GND), U5.9 (EP), U6.2 (GND); also elsewhere on the board
unnamed: C13.1, R17.2
unnamed: D8.2 (A), Q7.1 (G), R13.1
unnamed: D10.2 (A), R18.2
unnamed: D11.2 (A), R20.2
unnamed: C6.1, U5.1 (BST)
unnamed: C14.1, R17.1, U5.6 (COMP)
unnamed: C8.2, R14.2, R15.1, U5.5 (FB)
unnamed: R16.1, U5.4 (RT/CLK)
unnamed: C17.2, R19.2, R21.1, U6.5 (FB)
SW_3V3: L2.1, U6.3 (SW)
SW_5V: C6.2, L1.1, U5.8 (SW)
VIN_PROT: C11.1, D8.1 (K), D9.1 (K), J48.1, Q7.3 (S); also elsewhere on the board
VIN_RAW: F1.1, J17.1, J18.1; also elsewhere on the board

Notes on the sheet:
Voltage Input Protecton
3.3V Regulator
5V Regulator

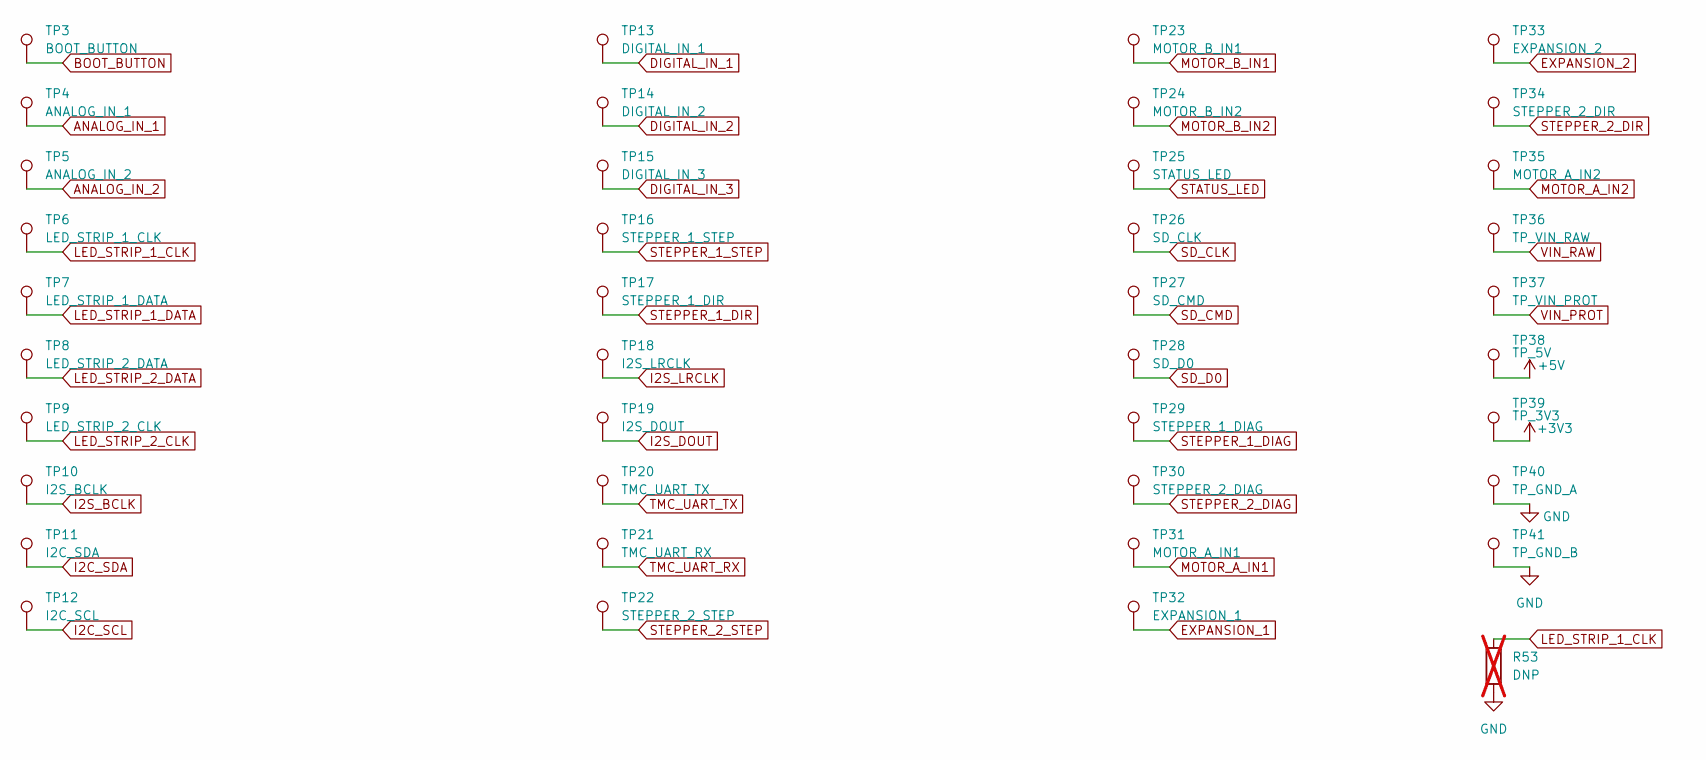
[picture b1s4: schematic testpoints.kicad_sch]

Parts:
R53: DNP; R_0603_1608Metric; not fitted
TP3: BOOT_BUTTON; TestPoint_Pad_1.5x1.5mm
TP4: ANALOG_IN_1; TestPoint_Pad_1.5x1.5mm
TP5: ANALOG_IN_2; TestPoint_Pad_1.5x1.5mm
TP6: LED_STRIP_1_CLK; TestPoint_Pad_1.5x1.5mm
TP7: LED_STRIP_1_DATA; TestPoint_Pad_1.5x1.5mm
TP8: LED_STRIP_2_DATA; TestPoint_Pad_1.5x1.5mm
TP9: LED_STRIP_2_CLK; TestPoint_Pad_1.5x1.5mm
TP10: I2S_BCLK; TestPoint_Pad_1.5x1.5mm
TP11: I2C_SDA; TestPoint_Pad_1.5x1.5mm
TP12: I2C_SCL; TestPoint_Pad_1.5x1.5mm
TP13: DIGITAL_IN_1; TestPoint_Pad_1.5x1.5mm
TP14: DIGITAL_IN_2; TestPoint_Pad_1.5x1.5mm
TP15: DIGITAL_IN_3; TestPoint_Pad_1.5x1.5mm
TP16: STEPPER_1_STEP; TestPoint_Pad_1.5x1.5mm
TP17: STEPPER_1_DIR; TestPoint_Pad_1.5x1.5mm
TP18: I2S_LRCLK; TestPoint_Pad_1.5x1.5mm
TP19: I2S_DOUT; TestPoint_Pad_1.5x1.5mm
TP20: TMC_UART_TX; TestPoint_Pad_1.5x1.5mm
TP21: TMC_UART_RX; TestPoint_Pad_1.5x1.5mm
TP22: STEPPER_2_STEP; TestPoint_Pad_1.5x1.5mm
TP23: MOTOR_B_IN1; TestPoint_Pad_1.5x1.5mm
TP24: MOTOR_B_IN2; TestPoint_Pad_1.5x1.5mm
TP25: STATUS_LED; TestPoint_Pad_1.5x1.5mm
TP26: SD_CLK; TestPoint_Pad_1.5x1.5mm
TP27: SD_CMD; TestPoint_Pad_1.5x1.5mm
TP28: SD_D0; TestPoint_Pad_1.5x1.5mm
TP29: STEPPER_1_DIAG; TestPoint_Pad_1.5x1.5mm
TP30: STEPPER_2_DIAG; TestPoint_Pad_1.5x1.5mm
TP31: MOTOR_A_IN1; TestPoint_Pad_1.5x1.5mm
TP32: EXPANSION_1; TestPoint_Pad_1.5x1.5mm
TP33: EXPANSION_2; TestPoint_Pad_1.5x1.5mm
TP34: STEPPER_2_DIR; TestPoint_Pad_1.5x1.5mm
TP35: MOTOR_A_IN2; TestPoint_Pad_1.5x1.5mm
TP36: TP_VIN_RAW; TestPoint_Pad_1.5x1.5mm
TP37: TP_VIN_PROT; TestPoint_Pad_1.5x1.5mm
TP38: TP_5V; TestPoint_Pad_1.5x1.5mm
TP39: TP_3V3; TestPoint_Pad_1.5x1.5mm
TP40: TP_GND_A; TestPoint_Pad_1.5x1.5mm
TP41: TP_GND_B; TestPoint_Pad_1.5x1.5mm

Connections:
+3V3: TP39.1 (1_1); also elsewhere on the board
+5V: TP38.1 (1_1); also elsewhere on the board
ANALOG_IN_1: TP4.1 (1_1); also elsewhere on the board
ANALOG_IN_2: TP5.1 (1_1); also elsewhere on the board
BOOT_BUTTON: TP3.1 (1_1); also elsewhere on the board
DIGITAL_IN_1: TP13.1 (1_1); also elsewhere on the board
DIGITAL_IN_2: TP14.1 (1_1); also elsewhere on the board
DIGITAL_IN_3: TP15.1 (1_1); also elsewhere on the board
EXPANSION_1: TP32.1 (1_1); also elsewhere on the board
EXPANSION_2: TP33.1 (1_1); also elsewhere on the board
GND: R53.2, TP40.1 (1_1), TP41.1 (1_1); also elsewhere on the board
I2C_SCL: TP12.1 (1_1); also elsewhere on the board
I2C_SDA: TP11.1 (1_1); also elsewhere on the board
I2S_BCLK: TP10.1 (1_1); also elsewhere on the board
I2S_DOUT: TP19.1 (1_1); also elsewhere on the board
I2S_LRCLK: TP18.1 (1_1); also elsewhere on the board
LED_STRIP_1_CLK: R53.1, TP6.1 (1_1); also elsewhere on the board
LED_STRIP_1_DATA: TP7.1 (1_1); also elsewhere on the board
LED_STRIP_2_CLK: TP9.1 (1_1); also elsewhere on the board
LED_STRIP_2_DATA: TP8.1 (1_1); also elsewhere on the board
MOTOR_A_IN1: TP31.1 (1_1); also elsewhere on the board
MOTOR_A_IN2: TP35.1 (1_1); also elsewhere on the board
MOTOR_B_IN1: TP23.1 (1_1); also elsewhere on the board
MOTOR_B_IN2: TP24.1 (1_1); also elsewhere on the board
SD_CLK: TP26.1 (1_1); also elsewhere on the board
SD_CMD: TP27.1 (1_1); also elsewhere on the board
SD_D0: TP28.1 (1_1); also elsewhere on the board
STATUS_LED: TP25.1 (1_1); also elsewhere on the board
STEPPER_1_DIAG: TP29.1 (1_1); also elsewhere on the board
STEPPER_1_DIR: TP17.1 (1_1); also elsewhere on the board
STEPPER_1_STEP: TP16.1 (1_1); also elsewhere on the board
STEPPER_2_DIAG: TP30.1 (1_1); also elsewhere on the board
STEPPER_2_DIR: TP34.1 (1_1); also elsewhere on the board
STEPPER_2_STEP: TP22.1 (1_1); also elsewhere on the board
TMC_UART_RX: TP21.1 (1_1); also elsewhere on the board
TMC_UART_TX: TP20.1 (1_1); also elsewhere on the board
VIN_PROT: TP37.1 (1_1); also elsewhere on the board
VIN_RAW: TP36.1 (1_1); also elsewhere on the board
